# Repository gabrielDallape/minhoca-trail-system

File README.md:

# MTS — Minhoca Trail System 🪱🧭

Sistema **"siga o líder"** por rádio **LoRa** para trilhas off-road: dois aparelhos idênticos, um **LÍDER** e um **SEGUIDOR**, conversam ponto-a-ponto. O líder anda e transmite o **trajeto** que fez (não só a posição); o seguidor plota um **mapa estilo Waze** (você no centro, o caminho do líder à frente, o rastro já percorrido, distância), pra seguir o líder mesmo sem vê-lo.

Nasceu como a Parte 2 de um projeto de odômetro.

```
   LÍDER (Waveshare 7B)                          SEGUIDOR (Waveshare 7B)
  ┌────────────────────┐                        ┌────────────────────┐
  │ GPS ─► grava rota   │   0x12 pos+trajeto    │  recebe ─► mapa Waze │
  │ route[] (~6 km)     │ ─────────────────────►│  roxo: a percorrer   │
  │                     │                        │  azul: percorrido    │
  │ recebe pos+ACK      │◄───────────────────── │  ► envia pos + ACK   │
  │ catch-up p/ o vão   │   0x11 pos+alerta+ACK  │                      │
  └────────────────────┘        LoRa P2P         └────────────────────┘
```

## Arquitetura atual (2 telas Waveshare)

O projeto passou por várias fases de hardware (CYD líder + GIGA seguidor). A versão **atual e em uso** são **duas telas Waveshare ESP32-S3-Touch-LCD-7B** idênticas rodando o **mesmo firmware** (`grupo_ws/`). O papel é escolhido na tela inicial por toque:

- **CRIAR SALA** → vira **LÍDER** (grava o próprio trajeto e o envia).
- **ENTRAR** → vira **SEGUIDOR** (recebe o trajeto e navega em cima dele).

### Hardware por tela

| Componente | Detalhe |
|---|---|
| Placa | Waveshare ESP32-S3-Touch-LCD-7B (RGB 1024×600, PSRAM 8MB) |
| Touch | GT911 (I2C 0x5D via Wire nos GPIO 8/9) |
| Expansor IO | CH32V003 (I2C 0x24) — controla painel, backlight, reset do touch |
| GPS | u-blox (NMEA 9600) no **GPIO6** (Serial2 RX) |
| Rádio | Radioenge LoRaMESH 915 MHz (Serial1, **GPIO 44/43**) |
| Gráfico | LovyanGFX + LGFX_Sprite (double-buffer na PSRAM) |

> ⚠️ **Isolar o LoRa do GPS na montagem.** Um contato acidental entre os pinos dos dois módulos causa curto e esquentamento. Use fita/espaçador entre eles.

## Funcionalidades

- **Mapa heading-up** com você no centro, anéis de distância (radar) e norte.
- **Cores do caminho** (fixas, independem do tema): **roxo** = caminho a percorrer até o líder; **azul** = rastro já percorrido.
- **Trajeto real** (breadcrumb): o líder envia o histórico de pontos do caminho, não uma linha reta — o seguidor remonta as curvas.
- **Alerta**: qualquer um aperta o botão → o **trecho do caminho entre os dois carros fica vermelho** + **borda vermelha piscando** na tela.
- **Perda de sinal**: **borda laranja piscando** nos dois — texto **"REDUZA"** no líder (pra diminuir a velocidade) e **"SINAL PERDIDO"** no seguidor.
- **Catch-up**: ao reconectar, o líder reenvia o trecho perdido em blocos rápidos até o seguidor alcançar — **preenche o vão de verdade**, sem linha reta pontilhada.
- **Fora do trajeto**: se o seguidor se afasta do caminho, **borda amarela piscando** + **"FORA DO TRAJETO"**.
- **Buffer de ~6 km** de trajeto na memória (PSRAM), o traçado não some conforme anda.
- **Zoom** +/− por toque, seletor de **tema** (Rally/Tático/HUD), nome da tela editável.

**Prioridade das bordas** (se coincidirem): vermelho (alerta) → laranja (perda) → amarelo (fora do trajeto).

## Protocolo LoRa (ponto-a-ponto)

Par fixo: líder = id 0, seguidor = id 1. Escravo transmite com o próprio id; mestre endereça ao destino.

- **`0x11` — seguidor → líder**: `[flags(bit0=fix, bit1=alert, bit2=temTrajeto)] [lat i32 LE ×1e7] [lon i32 LE ×1e7] [lastSeq u16 LE]`.
  O `lastSeq` é o **ACK** — até que ponto do trajeto o seguidor já tem — usado para o catch-up.
- **`0x12` — líder → seguidor**: `[flags(bit0=fix, bit1=alert, bit3=catchup)] [lat] [lon] [N] [seqBase u16 LE]` + `N × (lat i32, lon i32)`.
  Envia posição + um bloco do trajeto começando em `seqBase`. Fluxo normal manda os últimos pontos; em catch-up (seguidor muito atrás) reenvia a partir de `ACK+1` em blocos, acelerando para ~3 Hz até alcançar.

O seguidor só aceita pontos **contíguos** (evita buracos), ou um salto quando a flag de catch-up indica perda maior que o buffer.

Rádio travado no mesmo canal em ambas via `config_bps(BW500, SF7, CR4_5)` no setup.

## Estrutura do repositório

```
firmware/            EM USO (produção)
  trilha_core.h        núcleo compartilhado (protocolo, temas, estado, route[]/breadcrumb, geo)
  grupo_ws/            firmware das 2 telas Waveshare (líder e seguidor no mesmo binário)

                     FASE 4 (em construção, ver docs/RETOMAR.md)
  tdma_core.h          frames/slots do TDMA; fonte de tempo atrás de interface (beacon -> PPS)
  tile_pack.h          leitor de tiles do cartão por SETOR, sem filesystem (+ CRC32 por tile)
  e22_ping/            ping-pong SX1262 e MEDIÇÃO do tempo real de TX (dimensiona o slot)
  tdma_test/           TDMA de 3 nós com coordenadas falsas (conta colisão e desalinhamento)
  sd_bench/            mede CS pelo expansor I2C, custo de leitura e contenção do painel RGB
  tdma_selftest/       auto-teste da matemática do TDMA — roda em qualquer ESP32, sem periférico
  tile_selftest/       auto-teste do leitor de tiles — idem, sem cartão

tools/               Ferramentas
  build.ps1            compila/grava sem depender do PATH (arduino-cli vive na Arduino IDE)
  tiles/               pipeline do mapa offline: baixa, converte p/ RGB565, empacota, verifica
  ws_diag/ ws_hello/ ws_quiet/ ws_lcd_oficial/   tela/painel/touch
  ws_touch_diag/                                 GT911 (varre I2C, Product ID)
  ws_lora_scan/                                  acha os pinos do LoRa (UART2)
  ws_lora_cfg/                                   lê config do LoRaMESH (não-destrutivo)
  ws_lora_align/ ws_lora_commission/             alinha/comissiona o rádio
  giga_lora_cfg/                                 lê config do LoRa do GIGA
legacy/              Fases anteriores (referência histórica)
  odometro/            projeto original (Parte 1)
  cyd_* giga_* lora_* gps_* test_* ra8875_*   experimentos e etapas
  grupo/ grupo_giga_follow/ grupo_radio/       Modo Grupo no CYD/GIGA (descontinuado)
docs/                Planos, ambiente de build e ponto de retomada
```

## Fluxo de trabalho (gravar × usar)

A Waveshare tem **duas entradas USB-C**:
- **Porta USB nativa** (VID 303A) — usada para **gravar** o firmware e ler o serial/debug.
- **Porta UART1** (chip CH343, VID 1A86) — usada para **usar** em campo (só energia).

Regras aprendidas em campo:
- **Gravar** sempre pela porta USB nativa. As portas COM reenumeram muito — localize por VID 303A.
- **Usar** pela UART1 **com o switch em UART2** (a posição UART1 rouba os pinos 44/43 do LoRa).
- Abrir o serial na porta USB nativa **reseta a tela** — normal; por isso o uso em campo é pela UART1.

### GPS
- LED do GPS: **piscando 1×/s** = travou nos satélites (fix); **fixo/aceso** = ainda procurando.
- GPS **só pega a céu aberto** — atrás de vidro/telhado dá `sats=0` mesmo com o módulo perfeito. Cold start pode levar minutos.

## Build

Arduino CLI (core `esp32:esp32`). O `arduino-cli` vive dentro da instalação da
Arduino IDE e **não está no PATH** — use o script, que já carrega o caminho e o FQBN:

```powershell
.\tools\build.ps1 firmware\grupo_ws                        # compila (placa padrão: ws7b)
.\tools\build.ps1 firmware\tdma_test -Board devkit         # ESP32-S3-DevKitC
.\tools\build.ps1 firmware\grupo_ws -Upload -Port COM7     # grava
.\tools\build.ps1 x -ListPorts                             # acha a porta (VID 303A = USB nativa)
```

Bibliotecas: LovyanGFX, TinyGPSPlus, LoRaMESH, RadioLib. Versões exatas e tamanhos
de binário em [`docs/AMBIENTE_BUILD.md`](docs/AMBIENTE_BUILD.md).

## Status

**Produção (Fase 3):** duas telas Waveshare gravadas e validadas na bancada —
touch, LoRa (pareamento + troca de pacotes) e GPS (fix a céu aberto) OK nas duas.
*Pendente:* teste de campo com as duas em movimento (validar bordas, alerta
pintando o caminho e catch-up preenchendo a perda de sinal).

**Fase 4 (em construção):** rede de 25–50 nós com TDMA disciplinado por GPS e mapa
raster offline, rumo ao ESP32-P4 em ESP-IDF. A camada de TDMA e o leitor de tiles
estão escritos e validados por auto-teste; os sketches de rádio aguardam os
E22-900M30S. **Ponto de entrada: [`docs/RETOMAR.md`](docs/RETOMAR.md)** — pinagem,
o que medir em cada fase, lista de compras e lacunas em aberto.

> O rádio LoRaMESH **não pode fazer TDMA** (firmware de rede fechado atrás de UART,
> sem sinal de TxDone). Daí a migração para SX1262/RadioLib na Fase 4. O firmware de
> produção continua com o LoRaMESH e **não deve ser alterado** junto com a pilha nova.

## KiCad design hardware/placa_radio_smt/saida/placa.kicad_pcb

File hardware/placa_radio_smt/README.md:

# Placa do rádio v4: versão de fábrica (JLCPCB, SMT)

A mesma função da `placa_radio` v3 (o E22 atrás da tela de 7"), mas para **encomendar pronta**:
2 camadas, conectores de verdade e o step-down dentro da placa. **40 × 70 mm**, o mesmo espaço
da v3.

**O E22 não vem montado** (DNP): o footprint está na placa e você solda o módulo à mão. É a
peça mais cara, e os módulos já estão aqui.

## O que muda em relação à v3

| | v3 (laser) | v4 (fábrica) |
|---|---|---|
| Ligação com a tela | cabo PH cortado, fio soldado no pad | **J1/J2: JST-PH 12 vias**, cabo PH pronto |
| Alimentação | step-down solto, 5 V num pad | **J4: 12 V do carro** → fusível, diodo, TVS, buck AP63205 |
| GPS | fio soldado no pad do P3 | **J3: JST-PH 5 vias**, na ordem do NEO-7M (VCC GND TXD RXD PPS) |
| Antena | soldada no pad 21 | **no IPEX do próprio E22** (pad 21 fica livre) |
| Terra debaixo do E22 | face única | top inteiro em terra + 130 vias de costura, como a Ebyte pede |

## O circuito

**Entrada (J4, 12 V):** F1 (PTC 0,75 A) → D1 (SS34, protege contra inversão) → D2 (SMAJ18A).
- O TVS grampeia surtos do carro em ~29 V, abaixo dos 35 V absolutos do AP63205.
- O carro carregando (14,4 V) fica abaixo dos 18 V em que o TVS começa a conduzir.

**Buck (U2, AP63205WU, 5 V fixo, 2 A):** os valores são os da Tabela 2 do datasheet.
- L1 4,7 µH blindado, C4 10 µF/50 V na entrada, C7/C8 2 × 22 µF na saída, C6 100 nF no BST.
- O EN vai direto no VIN, como o datasheet permite.

**Do buck ao E22:**
- FB1 é uma ferrite de 600 Ω.
- Depois dela vem o banco do `ESTUDO_PECAS.md`, junto dos pinos 9/10: C1 220 µF eletrolítico **comum** (o ESR é o que amortece o surto), C2 10 µF e C3 100 nF.
- A nota AN2023005 da Ebyte sugere um LDO depois do DC-DC. De 5 V para 5 V não sobra folga para LDO, então a ferrite com o banco faz esse papel de filtro.

**R1 10 kΩ** segura o TXEN em 0 enquanto a tela liga.

**JP1 (jumper de cobre, já fechado)** liga o GND do P3, que é o terra do GPS, ao terra da placa.
- O `docs/MONTAGEM.md` mandava separar os dois terras no chicote. Lá o retorno de 600 mA do E22 voltava pela tela.
- Nesta placa o retorno vai direto para o 12 V e não passa pela tela. Por isso o jumper fica fechado.
- Se o PPS se mostrar sujo, corte o JP1 com estilete e compare antes e depois: é o teste que separa as duas hipóteses.

A lista completa de ligações, **lida da placa roteada**, está em `saida/fabrica/ligacoes.txt`.
Ela foi conferida pino a pino com o `docs/MONTAGEM.md`.

## Arquivos para a JLCPCB (`saida/fabrica/`)

| Arquivo | Onde vai |
|---|---|
| `GERBER_placa_radio_v4.zip` | "Add gerber file" |
| `BOM_placa_radio_v4.csv` | PCB Assembly → BOM |
| `CPL_placa_radio_v4.csv` | PCB Assembly → CPL (Pick & Place) |
| `ligacoes.txt` | conferência: cada rede e os pinos dela |
| `vista_cima.png`, `vista_baixo.png` | render da placa |

### Como pedir

1. **PCB:**
   - 2 camadas, 1,6 mm, 5 unidades, HASL sem chumbo;
   - cor de máscara à escolha;
   - "Remove Order Number": **Specify a location**. O lugar já está marcado no verso.
2. **PCB Assembly:**
   - **Economic**, Top side;
   - quantidade: **2 ou 5**. O mínimo da JLC é 2, e o custo fixo é o mesmo.
3. Suba o BOM e o CPL. O U1 (E22) e o JP1 não aparecem: é de propósito.
4. **Na pré-visualização, confira a rotação** destas peças:
   - U2 (pino 1 = bolinha);
   - D1, D2 (faixa = catodo, do lado de cima);
   - LED1;
   - C1 (+ para cima);
   - os 4 conectores.

   A JLC às vezes usa outro "zero" para o mesmo encapsulamento. Se alguma peça aparecer girada, corrija ali mesmo. O engenheiro da JLC também confere as peças polarizadas antes de montar.

### Quanto custa (estimativa de 2026-10-08, 5 placas, todas montadas)

Preços de peça e estoque lidos na API da JLC nesse dia. A taxa de montagem vem da página de
preços deles. **O imposto é a parte mais incerta.**

| Item | US$ |
|---|---|
| PCB 2 camadas 40 × 70, 5 un. | ~2–5 |
| Setup 8 + estêncil 1,5 | 9,5 |
| 8 peças "extended" × 3 (a JLC vem cobrando 1,50 em parte dos casos) | 12–24 |
| Peças: ~3,2 por placa × 5 | ~16 |
| Frete para o Brasil | ~15–25 |
| **Subtotal** | **~55–80** |

Com imposto de importação e ICMS, conte **~R$ 550–850 pelas 5**, ou **~R$ 110–170 por placa**.
Os E22 entram à parte.

As 8 peças "extended" são as que pagam taxa de setup: os 3 tipos de conector, U2, L1, C1, D2,
F1 e FB1. O resto é "basic" e não paga.

## Montagem depois que chegar

1. **Antes de soldar o E22:** ligue 12 V no J4 e meça **5,0 V** no pad do C1 (+). O LED verde acende.
2. Desligue. Solde o E22 com a **etiqueta para cima** e o **pino 1 no canto marcado** (embaixo, à direita).
   - Solde primeiro um pad de canto, confira o alinhamento e só então solde o resto.
3. **Antena no IPEX do módulo antes de energizar.**
4. **Cabo PH 12 vias:**
   - confira com o multímetro que o pino 1 da placa chega no pino 1 da tela (P1 → IO52);
   - existem cabos "mesmo sentido" e "invertidos", e a tela imprime os pinos na ordem inversa da numeração;
   - a pinagem inteira está gravada no verso da placa.
5. Primeiro boot a **10 dBm**.

## Como regenerar

```powershell
.\hardware\placa_radio_smt\gera.ps1
```

O fluxo roda no Docker (KiCad 9.0.9 e Freerouting 1.9; imagem em `docker/`):
1. `gera_pcb.py montar` posiciona as peças e liga as redes;
2. o Freerouting roteia;
3. `gera_pcb.py finalizar` enche o terra e costura;
4. o DRC roda;
5. Gerber, BOM, CPL e renders são exportados.

**Última execução: 0 violações, 0 pads desconectados.** `saida/placa.kicad_pcb` abre no KiCad
para ajuste à mão.

O footprint do E22 (`lib/`) é o oficial da LCSC (C411294), o mesmo que a v3 usou.

## O que não foi verificado

- **Nada foi fabricado ainda.** O DRC prova que a placa está desenhada direito; ele não prova que o circuito funciona.
- O buck segue o datasheet ao pé da letra, mas o layout dele foi espremido numa faixa de 9 mm. O laço quente (C4 → U2 → GND) ficou com ~3 mm. Se aparecer ruído no RF, é o primeiro suspeito.
- A rotação das peças no CPL é a do KiCad. Ver o passo 4 de "Como pedir".
- A altura: C1 tem 7,7 mm e os conectores verticais ~6 mm mais o cabo. Confira o vão atrás da tela.

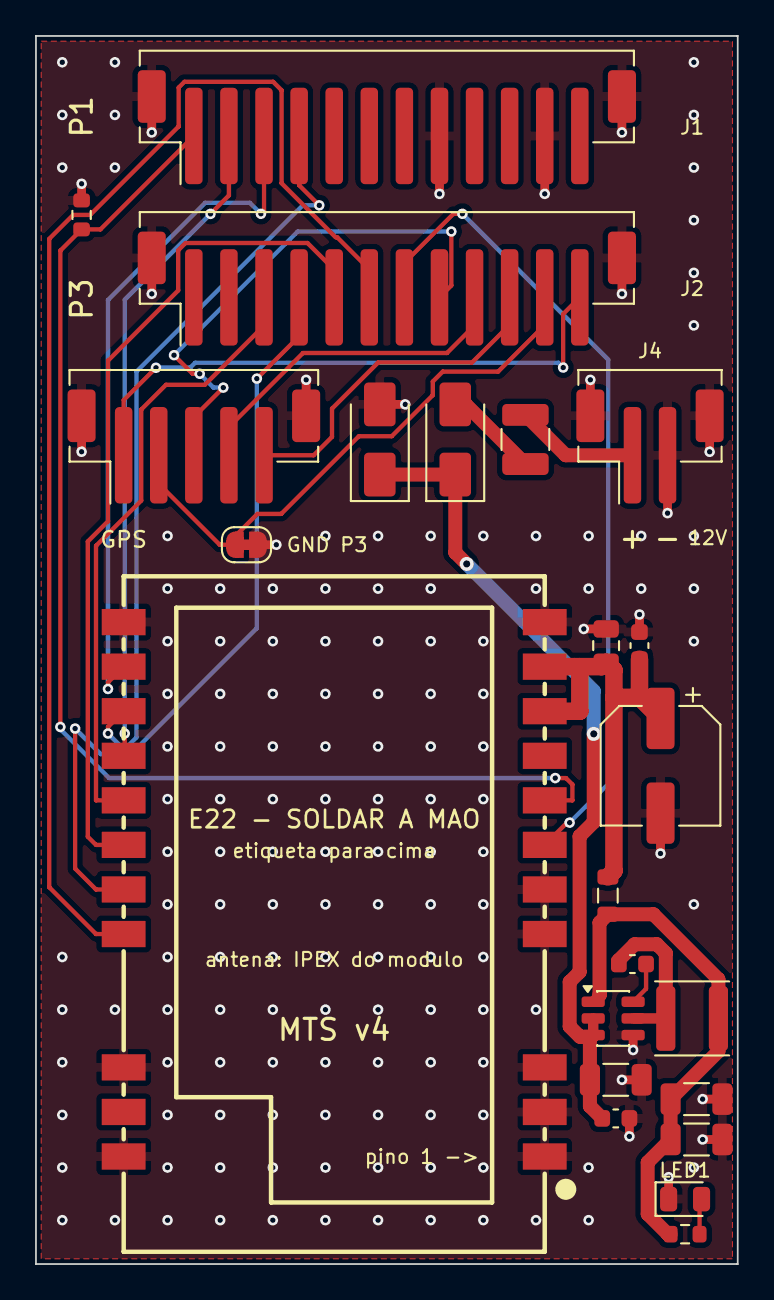
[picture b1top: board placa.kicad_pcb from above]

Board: 2 copper layers, 40.0 x 70.0 mm, 23 parts (0 on the bottom side), 23 nets.

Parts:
C1: 220 uF 16 V; CP_Elec_6.3x7.7
C2: 10 uF 25 V; C_0805_2012Metric
C3, C5, C6: 100 nF 50 V; C_0603_1608Metric
C4: 10 uF 50 V; C_1206_3216Metric
C7, C8: 22 uF 25 V; C_1206_3216Metric
D1: SS34; D_SMA
D2: SMAJ18A; D_SMA
F1: PTC 0,75 A 24 V; Fuse_1210_3225Metric
FB1: 600R 2 A; L_0805_2012Metric
J1: P1 tela; JST_PH_B12B-PH-SM4-TB_1x12-1MP_P2.00mm_Vertical
J2: P3 tela; JST_PH_B12B-PH-SM4-TB_1x12-1MP_P2.00mm_Vertical
J3: GPS; JST_PH_B5B-PH-SM4-TB_1x05-1MP_P2.00mm_Vertical
J4: 12V; JST_PH_B2B-PH-SM4-TB_1x02-1MP_P2.00mm_Vertical
JP1: GND P3; SolderJumper-2_P1.3mm_Bridged_RoundedPad1.0x1.5mm
L1: 4,7 uH; L_Changjiang_FNR4030S
LED1: verde; LED_0805_2012Metric
R1: 10k; R_0603_1608Metric
R2: 1k; R_0603_1608Metric
U1: E22-900M30S
U2: AP63205WU-7; TSOT-23-6

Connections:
3V3: J2.12, J3.1
5V_BUCK: C7.1, C8.1, FB1.1, L1.2, R2.1, U2.1
+5V: C1.1, C2.1, C3.1, FB1.2, U1.9, U1.10
BST: C6.2, U2.6
BUSY: J1.4, U1.14
DIO1: J1.3, U1.13
GND: C1.2, C2.2, C3.2, C4.2, C5.2, C7.2, C8.2, D2.2, J1.8, J1.11, J1.MP, J2.MP, J3.MP, J4.2, J4.MP, JP1.2, LED1.1, R1.2, U1.1, U1.2, U1.3, U1.4, U1.5, U1.11, U1.12, U1.20, U1.22, U2.4
GND_P3: J2.11, J3.2, JP1.1
GPS_RX: J2.9, J3.4
GPS_TX: J2.8, J3.3
LED_A: LED1.2, R2.2
MISO: J2.3, U1.16
MOSI: J2.5, U1.17
NRST: J1.2, U1.15
NSS: J2.6, U1.19
PPS: J2.10, J3.5
RXEN: J2.7, U1.6
SCK: J2.4, U1.18
SW: C6.1, L1.1, U2.5
TXEN: J1.1, R1.1, U1.7
VIN: F1.2, J4.1
VIN_F: D1.2, F1.1
VIN_P: C4.1, C5.1, D1.1, D2.1, U2.2, U2.3

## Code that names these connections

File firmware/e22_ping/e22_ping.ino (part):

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  #define PIN_MOSI  PIN_LORA_MOSI
  #define PIN_NSS   PIN_LORA_NSS
  #define PIN_BUSY  PIN_LORA_BUSY
  #define PIN_DIO1  PIN_LORA_DIO1
  #define PIN_NRST  PIN_LORA_NRST
  #define PIN_RXEN  PIN_LORA_RXEN
  #define PIN_TXEN  PIN_LORA_TXEN
#elif BOARD_DEVKIT
  #define PIN_SCK   12
  #define PIN_MISO  13
  #define PIN_MOSI  11
  #define PIN_NSS   10
  #define PIN_BUSY   9
  #define PIN_DIO1   8
  #define PIN_NRST  14
  #define PIN_RXEN  17
  #define PIN_TXEN  18
#else
  // Waveshare 7B, aperto de pinos: NRST em NC (amarrar no 3V3 com pull-up).
  #define PIN_SCK   12
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  #define PIN_MOSI  11
  #define PIN_NSS   15
  #define PIN_BUSY  16
  #define PIN_DIO1  43
  #define PIN_NRST  RADIOLIB_NC
  #define PIN_RXEN  44
  #define PIN_TXEN  RADIOLIB_NC   // <- nao ha pino: o PA nao vai ligar. Ver aviso.
#endif

// TESTE DE FIO TROCADO: BUSY <-> DIO1.
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#define TROCA_BUSY_DIO1 0
#if TROCA_BUSY_DIO1 && BOARD_P4
  #undef  PIN_BUSY
  #undef  PIN_DIO1
  #define PIN_BUSY  PIN_LORA_DIO1
  #define PIN_DIO1  PIN_LORA_BUSY
#endif

// ---------------------------------------------------------------- radio RF
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#define BEACON_MS 1000

SPIClass    spiLoRa(FSPI);
SX1262      radio = new Module(PIN_NSS, PIN_DIO1, PIN_NRST, PIN_BUSY, spiLoRa, SPISettings(2000000, MSBFIRST, SPI_MODE0));
Preferences prefs;

uint8_t nodeId = 0;
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bool txEmVoo = false;             // ha um startTransmit sem TxDone correspondente
uint32_t txStartUs = 0, seqOut = 0;
uint32_t rxOk = 0, rxBad = 0, lostCnt = 0;
uint32_t irqEstranha = 0;         // pulso no DIO1 sem nenhum flag no chip
uint32_t lastSeqIn = 0; bool haveSeqIn = false;
uint32_t lastBeacon = 0, lastReport = 0;
// estatistica do tempo de TX medido (startTransmit -> txDone). E O NUMERO QUE
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  uint32_t n49 = 0, n50 = 0, t0 = micros();
  while (micros() - t0 < 5000) {
    n49 += digitalRead(PIN_LORA_BUSY);   // o GPIO que o hardware.h chama de BUSY
    n50 += digitalRead(PIN_LORA_DIO1);   // o GPIO que o hardware.h chama de DIO1
  }
  Serial.printf("[fios] apos o reset: GPIO%d alto %lu vezes, GPIO%d alto %lu vezes\n",
                PIN_LORA_BUSY, (unsigned long)n49, PIN_LORA_DIO1, (unsigned long)n50);
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int configuraRadio(){
  int st = radio.begin(RF_FREQ, RF_BW, RF_SF, RF_CR, RF_SYNC, RF_PWR, RF_PRE, RF_TCXO);
  if (st != RADIOLIB_ERR_NONE) return st;
  // ARMADILHA 1: sem setRfSwitchPins o PA nunca liga. ORDEM: (rxEn, txEn).
  radio.setRfSwitchPins(PIN_RXEN, PIN_TXEN);
  // ARMADILHA 2: OCP padrao (~60mA) estrangula a potencia. Liberar p/ ~1W.
  radio.setCurrentLimit(RF_OCP);
  // NOTA DE DEFEITO (2026-08-24): um dos tres modulos (o que estava na tela A)
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  radio.clearIrqFlags(0xFFFFUL);
  radio.startReceive();
  delay(50);
  detachInterrupt(digitalPinToInterrupt(PIN_DIO1));
  brutoCnt = 0;
  attachInterrupt(digitalPinToInterrupt(PIN_DIO1), onBruto, RISING);
  delay(3000);
  detachInterrupt(digitalPinToInterrupt(PIN_DIO1));
  Serial.printf("[vigia] %lu bordas de subida em 3 s\n", (unsigned long)brutoCnt);
  if (brutoCnt == 0) {
    Serial.println("[vigia] ZERO. O radio em repouso nao gera borda nenhuma.");
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  }
}

// QUEM MANDA NO PINO DO DIO1?
// Teste classico de continuidade feito por software, sem multimetro: ligo o
// pull-up interno e vejo se o pino sobe. Se subir, nao ha nada do outro lado -
// o fio esta solto. Se ficar baixo ATE com pull-up, e porque o E22 esta
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  //    3 ms e concluiu "instavel" de um pino que estava simplesmente alto - janela
  //    curta demais para ver um evento de 0,5 s. Aqui tambem conto as TRANSICOES,
  //    que e o que separa "preso em alto" de "oscilando rapido".
  pinMode(PIN_DIO1, INPUT);
  int alto = 0, trans = 0, ant = digitalRead(PIN_DIO1);
  for (int i = 0; i < 1000; i++) {
    int v = digitalRead(PIN_DIO1);
    alto += v;
    if (v != ant) { trans++; ant = v; }
    delayMicroseconds(1000);
  }
  Serial.printf("[diag] DIO1 (GPIO%d) em 1 s: %d/1000 alto, %d transicoes\n",
                PIN_DIO1, alto, trans);

  // 3) so agora o teste de continuidade, e com janela longa o bastante.
  pinMode(PIN_DIO1, INPUT_PULLUP);   delay(5);
  int nUp = 0; for (int i = 0; i < 200; i++) { nUp += digitalRead(PIN_DIO1); delayMicroseconds(200); }
  pinMode(PIN_DIO1, INPUT_PULLDOWN); delay(5);
  int nDn = 0; for (int i = 0; i < 200; i++) { nDn += digitalRead(PIN_DIO1); delayMicroseconds(200); }
  pinMode(PIN_DIO1, INPUT);
  Serial.printf("[diag] pull-up %d/200 alto | pull-down %d/200 alto\n", nUp, nDn);

  if (nUp >= 190 && nDn <= 10) {
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#if BOARD_P4
  Serial.printf("[pin] placa P4 (MTS_PLACA=%d): SCK=%d MISO=%d MOSI=%d NSS=%d\n",
                MTS_PLACA, PIN_SCK, PIN_MISO, PIN_MOSI, PIN_NSS);
  Serial.printf("[pin] BUSY=%d DIO1=%d NRST=%d RXEN=%d TXEN=%d\n",
                PIN_BUSY, PIN_DIO1, PIN_NRST, PIN_RXEN, PIN_TXEN);
#elif !BOARD_DEVKIT
  Serial.println("[AVISO] nem P4 nem devkit: nao ha pino p/ TXEN nesta placa.");
  Serial.println("        Sem TXEN o PA do E22 NAO liga -> 'transmite nada'.");
  Serial.println("        Use um P4 ou um devkit p/ a bancada de radio.");
#endif
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  uint32_t t0 = micros();
  int st = radio.startTransmit(p, PKT_N);
  for (int i = 0; i < 300; i++) {
    amostra[i] = (digitalRead(PIN_BUSY) ? 1 : 0) | (digitalRead(PIN_DIO1) ? 2 : 0);
    while ((int32_t)(micros() - t0) < (int32_t)((i + 1) * 1000)) { }
  }

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}

void testeGps(){
  Serial.printf("[gps] Serial1 em %d bps, RX=GPIO%d TX=GPIO%d, PPS=GPIO%d\n",
                GPS_BAUD, PIN_GPS_RX, PIN_GPS_TX, PIN_GPS_PPS);
  Serial1.begin(GPS_BAUD, SERIAL_8N1, PIN_GPS_RX, PIN_GPS_TX);

  pinMode(PIN_GPS_PPS, INPUT);
  ppsCnt = 0; ppsUltimoUs = 0; ppsIntervaloUs = 0;
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  Serial.printf("[gps] PPS: %lu pulsos em 6 s", (unsigned long)ppsCnt);
  if (ppsIntervaloUs) Serial.printf(", ultimo intervalo %lu us", (unsigned long)ppsIntervaloUs);
  if      (ppsReal)  Serial.print("  -> 1 Hz, e PPS de verdade");
  else if (ppsRuido) Serial.print("  -> RUIDO, nao e PPS: o pino esta solto");
  else if (ppsCnt)   Serial.print("  -> ritmo estranho, nao confie");
  Serial.println();

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    if (ppsReal) {
      Serial.printf("[gps] >>> NENHUM byte, MAS o PPS pulsa a 1 Hz. Logo o modulo tem 3V3, GND,\n");
      Serial.printf("[gps]     antena e fix - so o fio de DADOS nao chega.\n");
      Serial.printf("[gps]     Confira o TXD do GPS ate o GPIO%d. E so ele.\n", PIN_GPS_RX);
    } else {
      Serial.println("[gps] >>> NENHUM byte e nenhum PPS. O GPS nao esta ligado, ou o TXD");
      Serial.printf( "[gps]     dele nao chegou no GPIO%d, ou falta o 3V3/GND dele.\n", PIN_GPS_RX);
    }
  } else if (!frases) {
    Serial.println("[gps] >>> chegam bytes mas nao formam frase: baud errado.");
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      Serial.printf("[gps] >>> FIX! qualidade=%d, %d satelites\n", fix, sats);
      if (!ppsReal) {
        Serial.printf("[gps] >>> mas ZERO PPS. Ha fix, entao o pulso existe: o fio do\n");
        Serial.printf("[gps]     PPS nao chegou no GPIO%d. Sem PPS nao ha TDMA.\n", PIN_GPS_PPS);
      } else {
        Serial.println("[gps] >>> PPS pulsando. E a regua de tempo do TDMA - esta tudo pronto.");
      }
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

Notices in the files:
README.md:
License: MIT
